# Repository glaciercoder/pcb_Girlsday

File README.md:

# pcb_Girlsday
Has nothing to do with girlsday

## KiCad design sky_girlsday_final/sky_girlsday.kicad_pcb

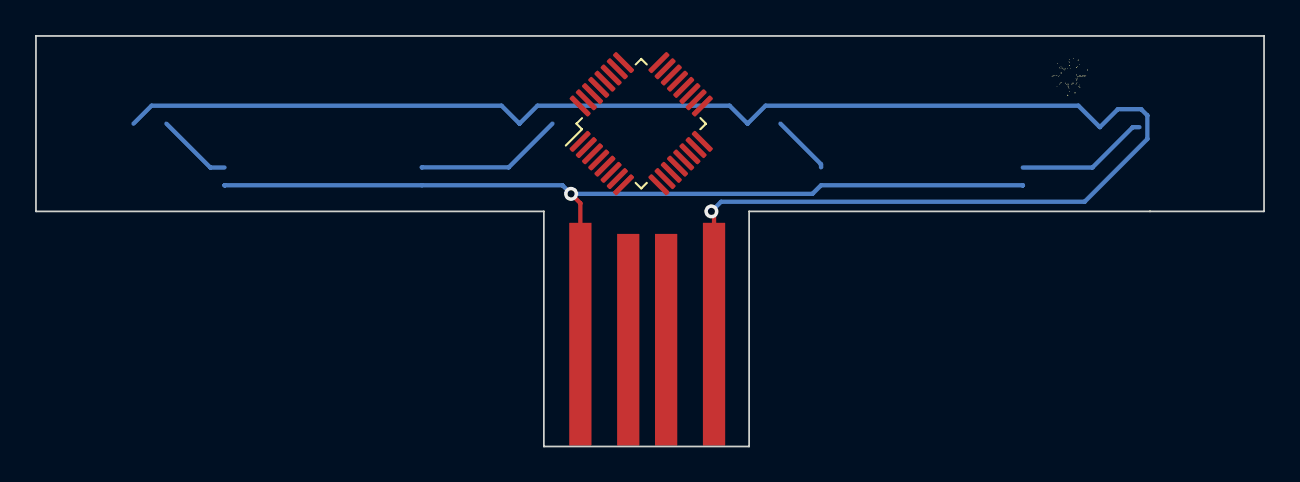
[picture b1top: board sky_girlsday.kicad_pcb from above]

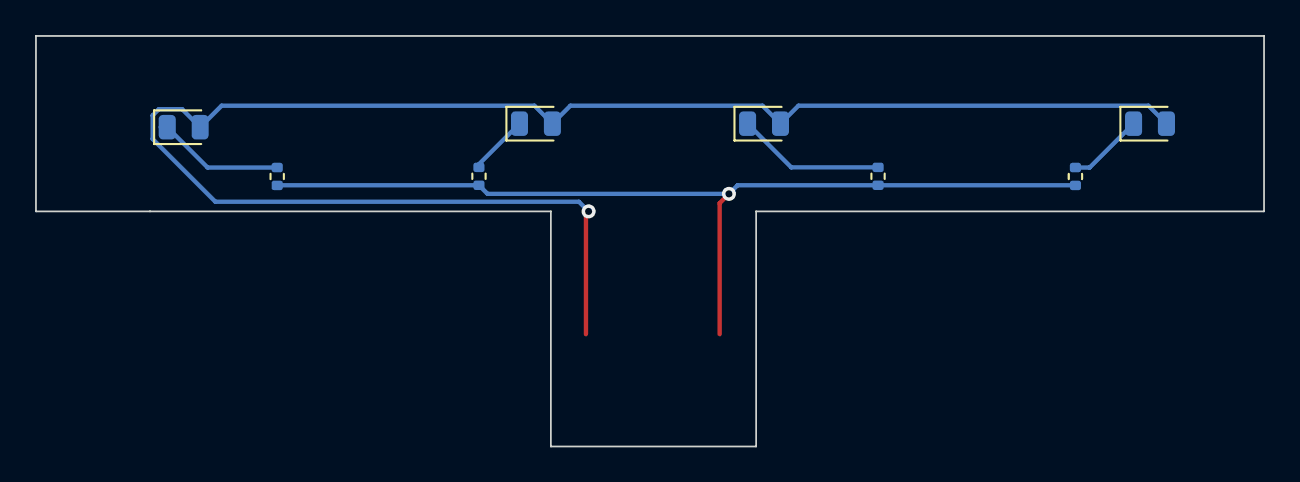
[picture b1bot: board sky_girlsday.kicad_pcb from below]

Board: 2 copper layers, 70.0 x 23.4 mm, 9 parts (8 on the bottom side), 6 nets.

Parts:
D1, D2, D3, D4: LED; LED_0805_2012Metric
J1: USB_A; gold_finger_USB
R1, R2, R3, R4: 2k2; R_0402_1005Metric

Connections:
+5V: J1.1, R1.2, R2.2, R3.2, R4.2
GND: D1.2, D2.2, D3.2, D4.2, J1.2
unnamed: D1.1, R1.1
unnamed: D2.1, R2.1
unnamed: D3.1, R3.1
unnamed: D4.1, R4.1

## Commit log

2021-02-04 unfinished schemes and useful datasheet
    1st day, find documents for the chips needed
2021-02-05 Add files via upload
    scheme draft finished
2021-03-07 Add files via upload
    Change the layer using txt tools
